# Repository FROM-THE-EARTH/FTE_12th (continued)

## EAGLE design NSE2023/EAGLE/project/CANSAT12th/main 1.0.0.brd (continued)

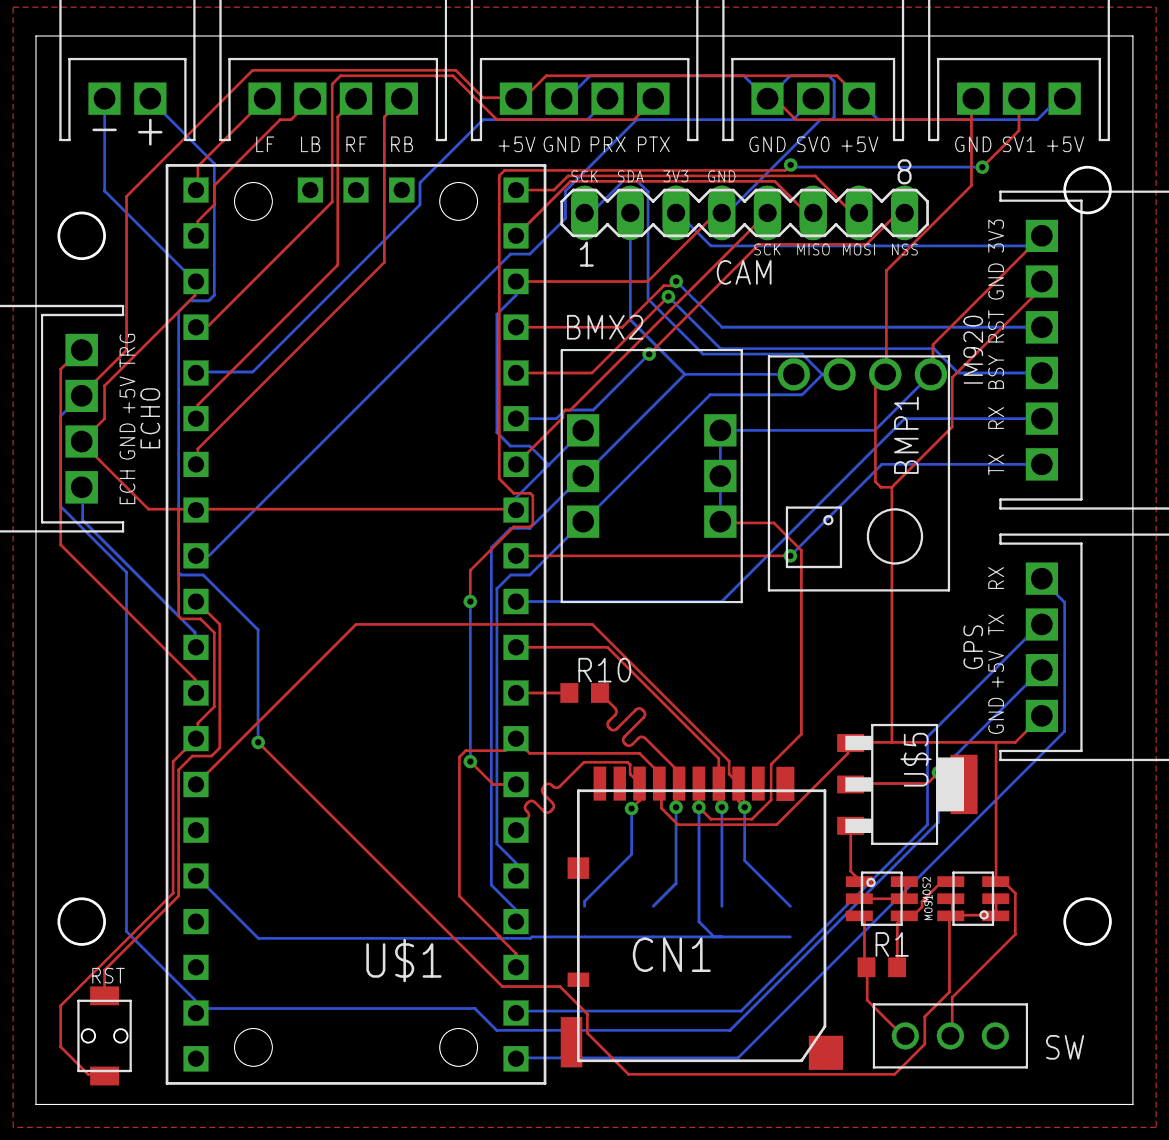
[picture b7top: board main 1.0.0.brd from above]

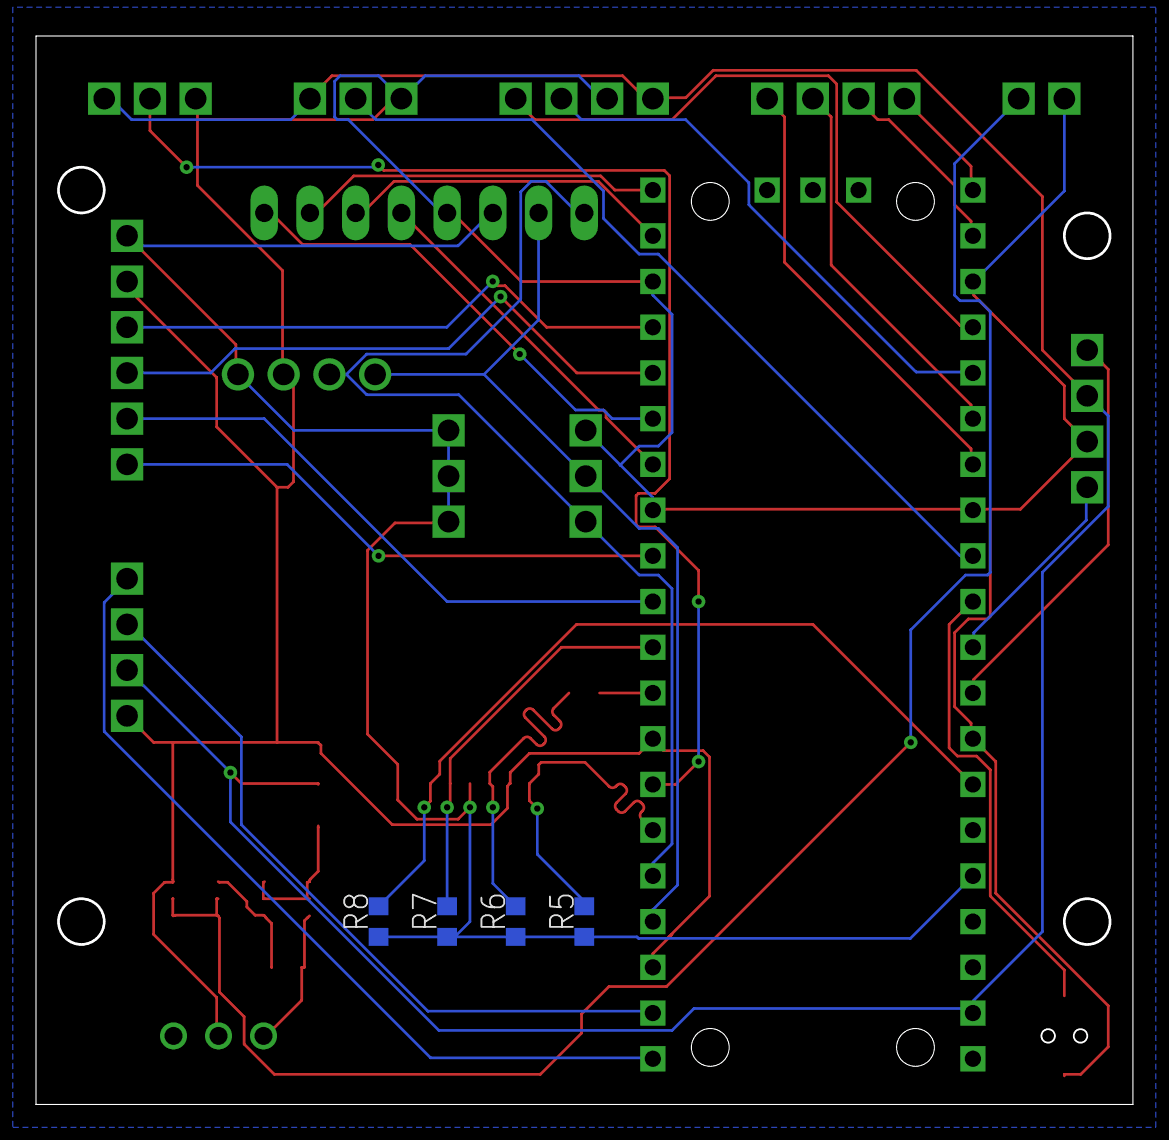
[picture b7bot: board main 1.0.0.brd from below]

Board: 2 copper layers, 60.8 x 59.2 mm, 24 parts (4 on the bottom side), 35 nets.

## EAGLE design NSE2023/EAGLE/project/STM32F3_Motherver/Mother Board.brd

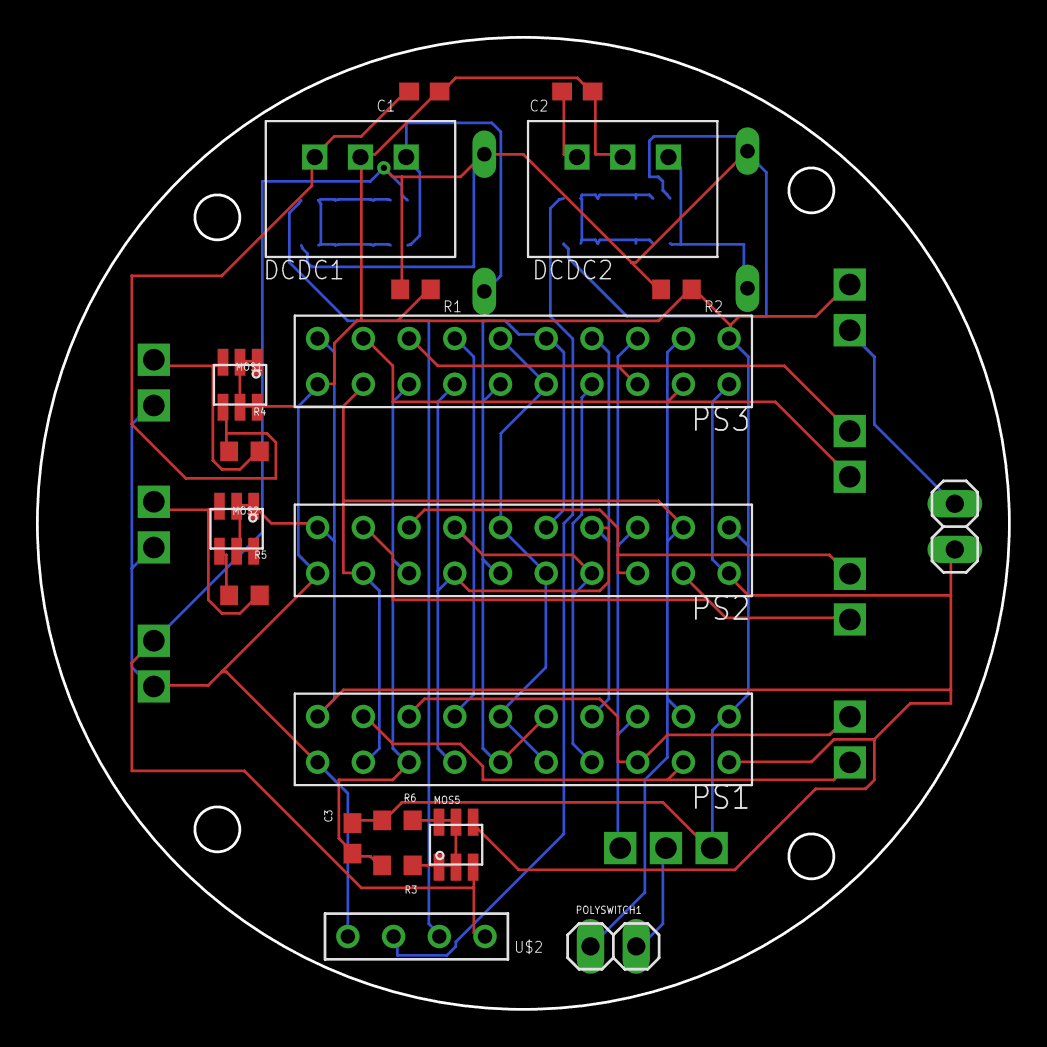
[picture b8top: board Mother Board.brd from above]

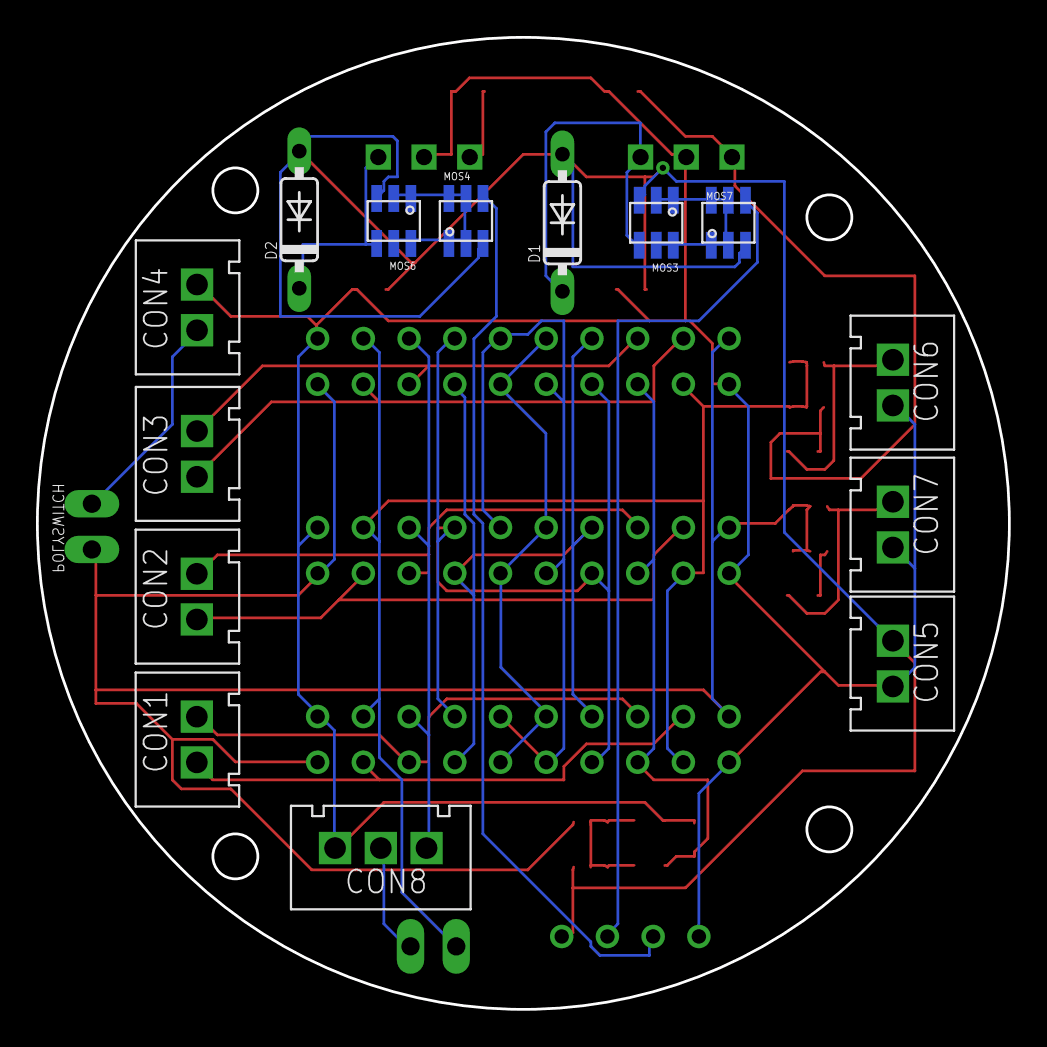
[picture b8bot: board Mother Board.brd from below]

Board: 2 copper layers, 54.0 x 54.0 mm, 34 parts (14 on the bottom side), 30 nets.

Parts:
C1, C2: 3.3uF; C0603
C3: 10uF; C0603
CON1, CON2, CON3, CON4, CON5, CON6, CON7: 2PIN
CON8: 3PIN
D1, D2: 1N4148DO35-7; DO35-7
DCDC1: 5V1A_M78AR05-1
DCDC2: 3.3V1A_M78AR033-1
MOS1, MOS2, MOS3, MOS4, MOS5, MOS6, MOS7: SSM6J808R
POLYSWITCH, POLYSWITCH1: 1X02
PS1, PS2, PS3: 2X10
R1, R2, R3: 1k; R0603
R4, R5: 100k; R0603
R6: 10k; R0603
U$2: 1X4

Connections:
3.3VSW: CON7.P$2, MOS2.3, R5.1
3.3V_ENT: C2.1, DCDC2.VOUT
3.3_RAW: CON4.P$2, POLYSWITCH.2
5VSW: CON6.P$2, MOS1.3, R4.1
5V_ENT: C1.1, DCDC1.VOUT, MOS1.4, R4.2
5V_ENT1: MOS2.4, R5.2
5V_RAW: CON8.P$2, POLYSWITCH1.2
7.4_0ENT: MOS7.4, U$2.P$2
7.4_1ENT: MOS4.4, U$2.P$3
+3V3: MOS2.1, MOS2.2, MOS2.5, MOS2.6, MOS5.4, POLYSWITCH.1, PS1.P$2, PS1.P$19, PS2.P$2, PS2.P$19, PS3.P$2, PS3.P$19
+5V: MOS1.1, MOS1.2, MOS1.5, MOS1.6, POLYSWITCH1.1, PS1.P$3, PS1.P$18, PS2.P$3, PS2.P$18, PS3.P$3, PS3.P$18
BIT1: PS1.P$9, PS1.P$12, PS2.P$9, PS2.P$12, PS3.P$9, PS3.P$12
BIT2: PS1.P$7, PS1.P$14, PS2.P$7, PS2.P$14, PS3.P$7, PS3.P$14
FP: CON5.P$2, D1.A, D2.A, MOS3.3, MOS4.3, MOS5.3, MOS6.3, MOS7.3, R1.2, R2.2, U$2.P$1
FP_CHECKER: C3.1, PS1.P$5, PS2.P$5, PS3.P$5, R3.2
GND: C1.2, C2.2, C3.2, CON4.P$1, CON5.P$1, CON6.P$1, CON7.P$1, CON8.P$1, DCDC1.GND, DCDC2.GND, PS1.P$1, PS1.P$20, PS2.P$1, PS2.P$20, PS3.P$1, PS3.P$20, R1.1, R2.1, R6.1, U$2.P$4
LOGRX: PS1.P$8, PS1.P$13, PS2.P$8, PS2.P$13, PS3.P$8, PS3.P$13
LOGTX: PS1.P$10, PS1.P$11, PS2.P$10, PS2.P$11, PS3.P$10, PS3.P$11
unnamed: D2.C, DCDC2.VIN, MOS6.4
unnamed: MOS4.1, MOS4.2, MOS4.5, MOS4.6, MOS6.1, MOS6.2, MOS6.5, MOS6.6
unnamed: D1.C, DCDC1.VIN, MOS3.4
unnamed: MOS3.1, MOS3.2, MOS3.5, MOS3.6, MOS7.1, MOS7.2, MOS7.5, MOS7.6
unnamed: MOS5.1, MOS5.2, MOS5.5, MOS5.6, R3.1, R6.2
PWM: CON8.P$3, PS1.P$16, PS2.P$16, PS3.P$16
SCL0: CON1.P$1, PS1.P$6, PS1.P$15
SCL1: CON2.P$1, PS2.P$6, PS2.P$15
SCL2: CON3.P$1, PS3.P$6, PS3.P$15
SDA0: CON1.P$2, PS1.P$4, PS1.P$17
SDA1: CON2.P$2, PS2.P$4, PS2.P$17
SDA2: CON3.P$2, PS3.P$4, PS3.P$17

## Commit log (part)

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2022-03-18 asdf
2022-03-18 qwds
2022-04-24 asdfgb
2022-04-27 add ble-app
2022-04-29 Create IM920
2022-05-06 add lbr via abe
2022-05-09 asdfg
2022-05-09 bdfsadsvfds
2022-05-09 asdfgh
2022-05-15 aaaaa
2022-05-16 Create cansat.s##
2022-05-16 kato
2022-05-17 a
    a
2022-06-05 kato_ESP
2022-06-06 asdsas
2022-06-06 sadasd
2022-06-06 fdfsfdvxb
2022-06-06 yoroshiku
2022-06-07 yoro
2022-06-07 repair1
2022-06-07 repair2
2022-06-07 sadfghddsfgnvbfadwfsgcnvbfadgscn
2022-06-08 version change
2022-06-08 asasa
2022-06-08 asdfgfdsasdfgfdsasdfgfdsa
2022-06-08 eagle_kato
2022-06-11 asdc
2022-06-11 ssad
2022-06-11 qasd
2022-06-11 PCB_kato
2022-06-11 asdfd
2022-06-12 battery_katoo
2022-06-12 rc_brd_kato
2022-06-12 imgs
2022-06-16 abehiroshijin
2022-06-18 13_practice
2022-07-27 aaaa
2022-08-06 change
2022-11-16 initialized tanekonn
2022-11-29 Add eagle library_1
    ヴァン、ふうか済
2022-12-02 ライブラリの修正
2022-12-04 add test projects
2022-12-06 version up
2022-12-06 removed waste
2022-12-08 最終調整
    ・パワー基板に穴あけ
    ・pcbgogoの基板チェック完了
2022-12-08 ガーバーデータ
    ガーバーデータの作製
2022-12-25 Create TRC_main1.0.0.s##
2023-01-04 add project
2023-02-08 noshir
2023-02-08 tonbo
2023-02-20 TRC2023 cansat first
2023-03-03 KATOONAMI
    KATOONAMI
2023-03-23 cerate folder
2023-03-23 add lib
2023-03-23 add bmp
2023-04-16 katoooo
2023-04-16 katoooooo
2023-04-24 add eagle lib kato
2023-04-24 update logbord
2023-04-25 kato_logbord
2023-05-17 add PCB
2023-05-21 Create Mother Board.s##
2023-05-21 death
2023-05-23 kato update logbord
2023-05-29 edit mother
2023-05-30 edit pcb
2023-06-04 edit logger
2023-06-24 Create radio.b##
2023-07-10 change image size
    メリットパートの画像の大きさを変更
2023-07-14 edit mother board
2023-07-15 update rocket controller
2023-07-21 create new board design NSE2023 RAY
    最終版基板の設計用ディレクトリを作成
2023-07-21 edit rocket controller
    PWMの出力をTIM２ピンに変更
2023-07-21 edit logboard
2023-07-24 create final board NSE2023
2023-07-27 create final board
2023-07-28 add gerver data
2023-08-02 Create STM32F3logbordv2.b##
2023-08-12 Create STM32F3logbordv2.s##
2023-08-12 update logger
2023-08-15 create new project
2023-08-15 Create Mother Board_ver2.0.0.b##
2023-08-17 create logger programm
2023-08-17 update logger, downlink
2023-08-30 Update STM32F3logbordv2.s##
2023-10-13 organize NSE2023 workspace
2023-10-31 addfiles
    addfiles
2023-10-31 add cad
2023-10-31 STM32の開発ワークスペースを作成
2023-10-31 edit README
2023-10-31 READMEを編集
2023-10-31 画像を追加
